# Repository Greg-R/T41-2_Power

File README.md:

The documentation for this module is located here:

<https://kf5n.com/t41-2/t41-2_power/>

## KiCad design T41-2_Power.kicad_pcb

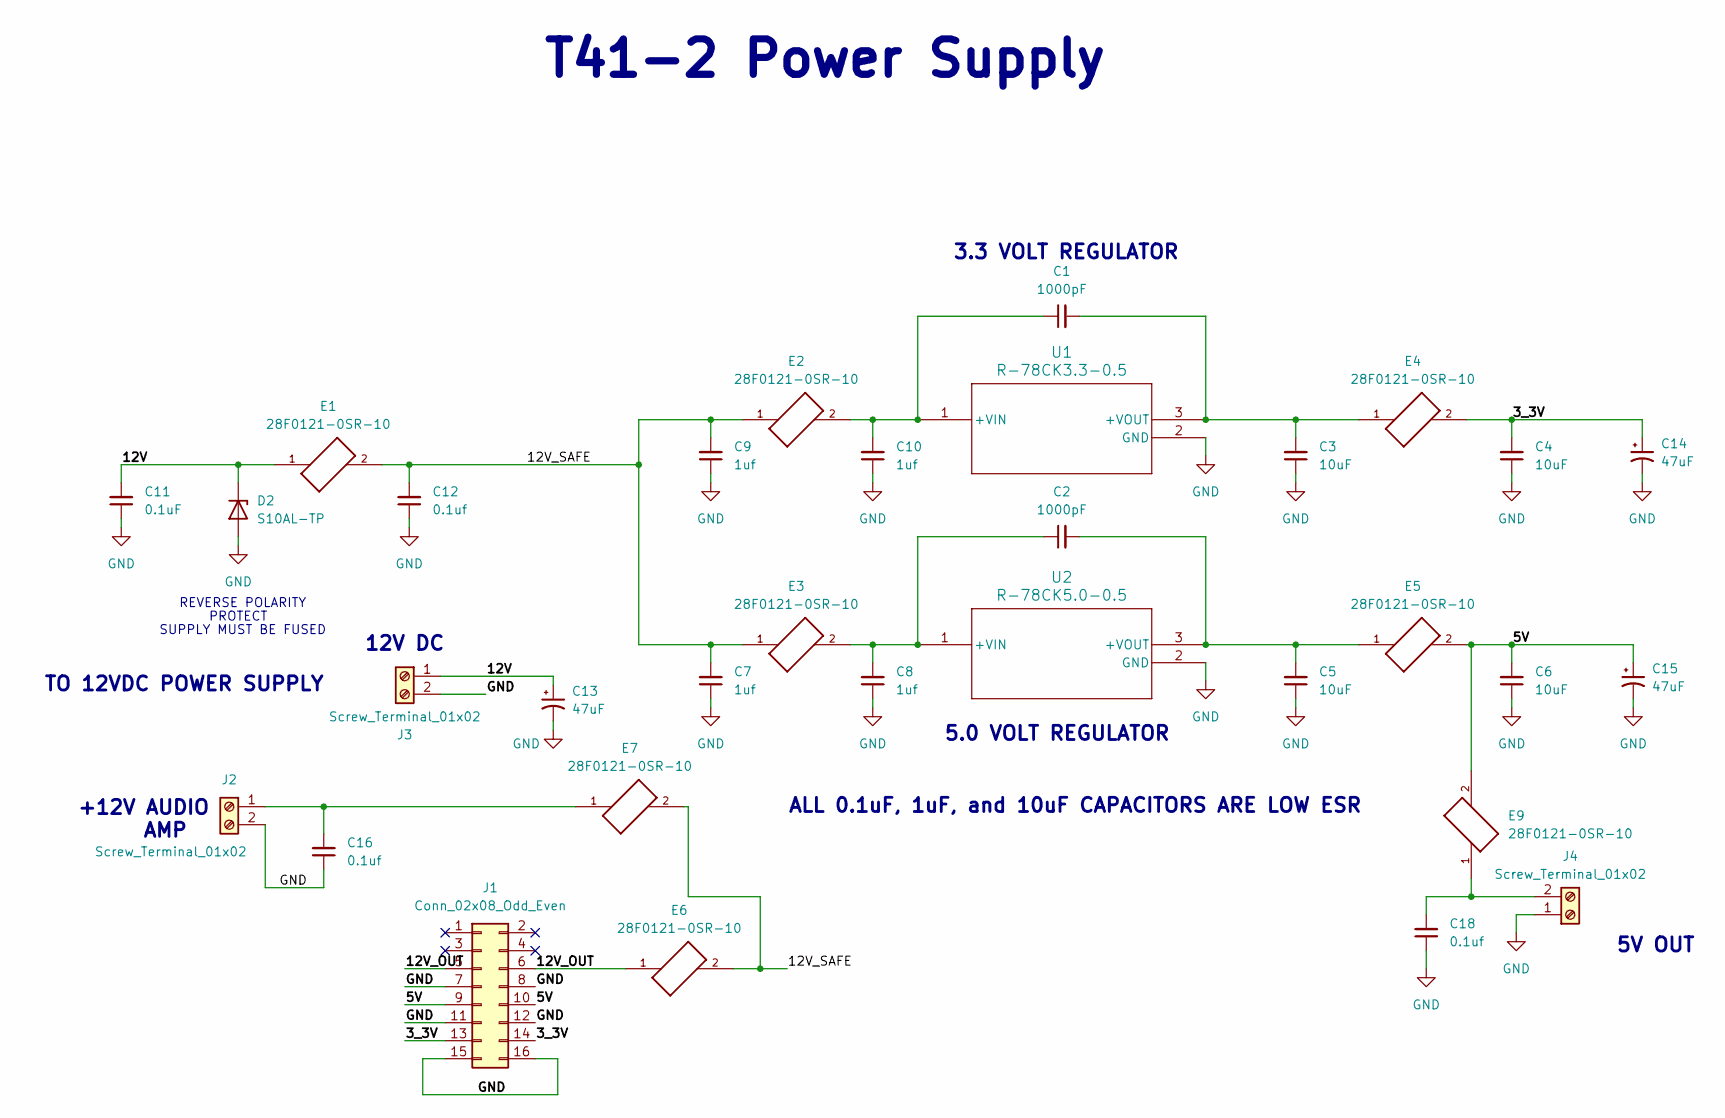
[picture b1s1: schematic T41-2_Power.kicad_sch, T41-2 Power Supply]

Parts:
C1, C2: 1000pF; C_1206_3216Metric
C3, C4, C5, C6: 10uF; C_1206_3216Metric
C7, C8, C9, C10: 1uf; C_1206_3216Metric
C11: 0.1uF; C_1206_3216Metric
C12, C16, C18: 0.1uf; C_1206_3216Metric
C13, C14, C15: 47uF; CP_Elec_6.3x5.7
D2: S10AL-TP; D_SMC
E1, E2, E3, E4, E5, E6, E7, E9: 28F0121-0SR-10; FB_28F0121-0SR-10; PARTREV J
J1: Conn_02x08_Odd_Even; IDC-Header_2x08_P2.54mm_Vertical
J2, J3, J4: Screw_Terminal_01x02; TerminalBlock_Philmore_TB132_1x02_P5.00mm_Horizontal
U1: R-78CK3.3-0.5; CONV_R-78CK5.0-0.5
U2: R-78CK5.0-0.5; CONV_R-78CK5.0-0.5

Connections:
/3_3V: C4.2, C14.1, E4.2, J1.13, J1.14
/5V: C6.2, C15.1, E5.2, E9.2, J1.9, J1.10
/12V: C11.2, C13.1, D2.1 (K), E1.1, J3.1
/12V_OUT: E6.1, J1.5, J1.6
/12V_SAFE: C7.2, C9.2, C12.2, E1.2, E2.1, E3.1, E6.2, E7.2
GND: C3.1, C4.1, C5.1, C6.1, C7.1, C8.1, C9.1, C10.1, C11.1, C12.1, C13.2, C14.2, C15.2, C16.1, C18.1, D2.2 (A), J1.7, J1.8, J1.11, J1.12, J1.15, J1.16, J2.2, J3.2, J4.1, U1.2 (GND), U2.2 (GND)
unnamed: C16.2, E7.1, J2.1
unnamed: C18.2, E9.1, J4.2
unnamed: C1.1, C10.2, E2.2, U1.1 (+VIN)
unnamed: C1.2, C3.2, E4.1, U1.3 (+VOUT)
unnamed: C2.1, C8.2, E3.2, U2.1 (+VIN)
unnamed: C2.2, C5.2, E5.1, U2.3 (+VOUT)

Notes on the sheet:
SUPPLY MUST BE FUSED
+12V AUDIO AMP
T41-2 Power Supply
3.3 VOLT REGULATOR
ALL 0.1uF, 1uF, and 10uF CAPACITORS ARE LOW ESR
12V DC
REVERSE POLARITY
5V OUT
PROTECT
TO 12VDC POWER SUPPLY
5.0 VOLT REGULATOR

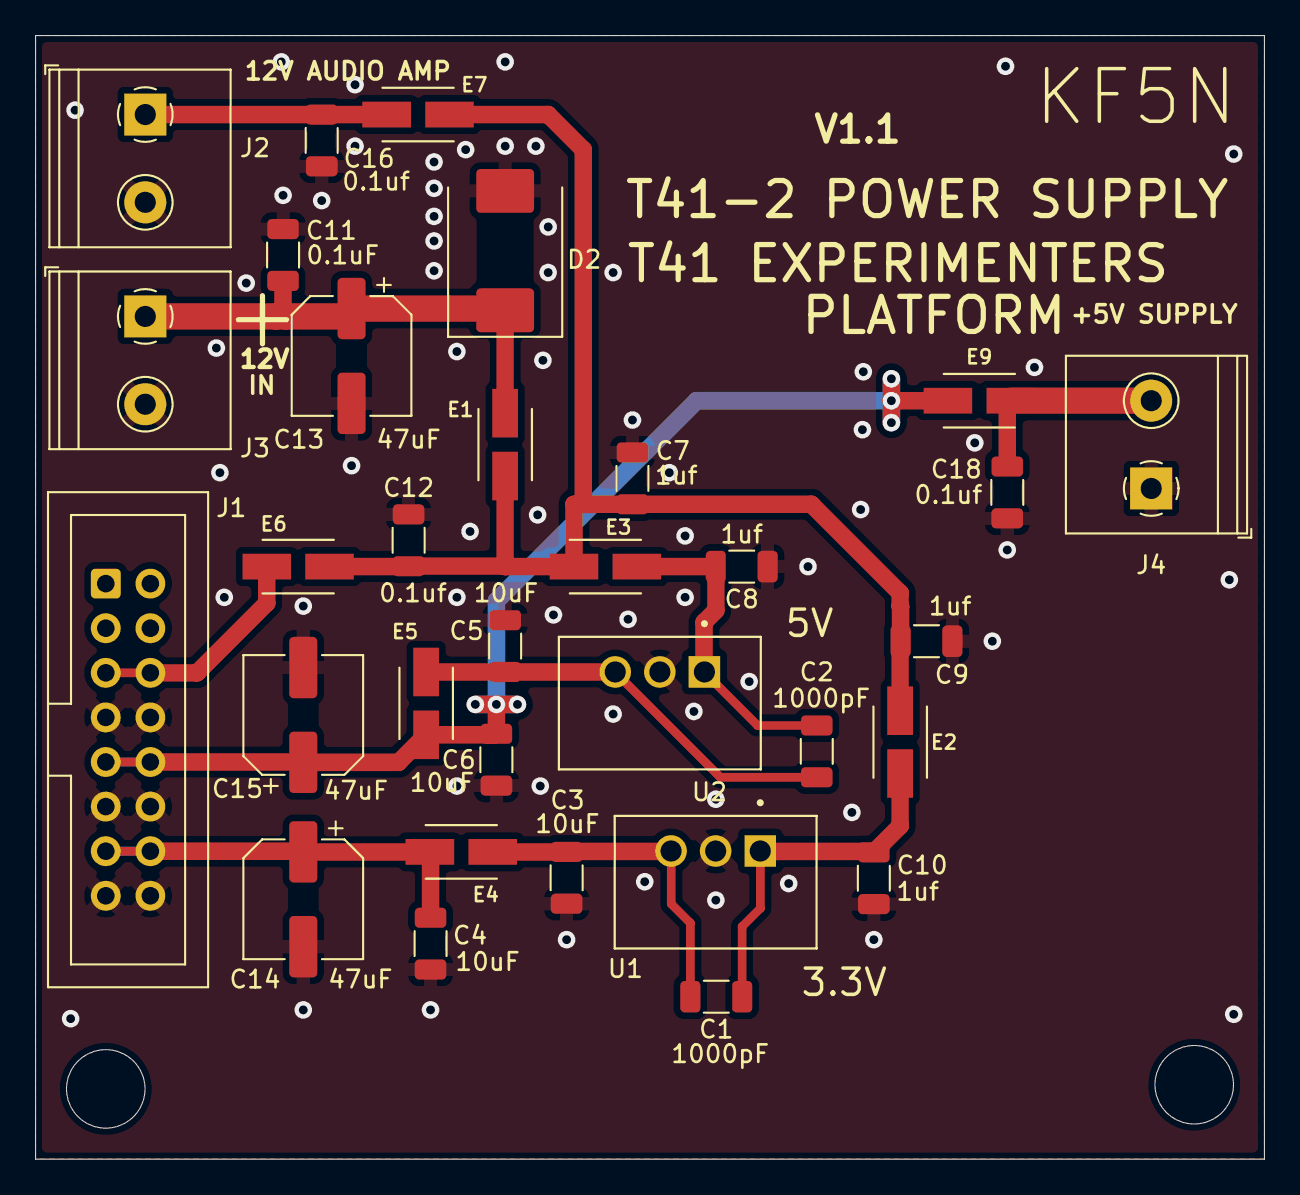
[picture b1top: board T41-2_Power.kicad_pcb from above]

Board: 2 copper layers, 70.0 x 64.0 mm, 32 parts (0 on the bottom side), 12 nets.

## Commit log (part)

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2024-05-11 Added 5V outlet for display power.
2024-05-11 Updated PDF schematic.
2024-05-11 Updated gerbers, ready for fab V1.0.
2024-06-12 Added + indicator in silkscreen for 5V output.
2024-06-12 Finished preliminary README.
2024-06-12 Minor revisions to README.
2026-04-22 Updated schematic with note on V10/V11 versus T41-2 speaker connection.
